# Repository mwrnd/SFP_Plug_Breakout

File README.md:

**Work-in-Progress** - [First Revision gerbers being tested](https://github.com/mwrnd/SFP_Plug_Breakout/releases/tag/v0.1-alpha).

# SFP_Plug_Breakout

Pluggable [SFP (SFF INF-8074i)](https://members.snia.org/document/dl/26184) and [SFP+ (SFF-8432)](https://members.snia.org/document/dl/25892) Module Breakout for developing SFP modules. PCB must be manufactured with a **1.0mm** thickness.

Similar Projects: [SFP-Breakout-Board](https://github.com/aewallin/SFP-Breakout-Board/tree/df46707f1ecbe9b7fed1791247dec31a45b60560), [SFP_BreakoutBoard](https://github.com/kingyoPiyo/SFP_BreakoutBoard), [SFP-Loopback-Board](https://github.com/aewallin/SFP-Loopback-Board), and [Sfp-breakout](https://osmocom.org/projects/misc-hardware/wiki/Sfp-breakout)(*osmocom.org*).

One trivial use is an [SFP Loopback](https://www.fs.com/products/109371.html):

## PCB Layout

Differential pair parameters were calculated based on a **board thickness of 1.0mm**.

## Schematic

The 0.1" Header is designed to accept jumpers for the **TX_FAULT**, **RX_LOS**, **TX_DISABLE**, and optionally **Rate-Select** signals.

**TX_FAULT**, **RX_LOS**, and **TX_DISABLE** jumpers need to be mounted for normal operation. These signals are pulled up to Vcc with 10k resistors but are Active-Low.

## Bill Of Materials

I have been testing with general purpose capacitors for the RX and TX DC-Blocking capacitors (C1, C2, C3, C4) but at <10Gbps bitrates. Capacitors will need to be sized smaller, 0402 or even 0201, and more effort would need to go into their selection for high bitrates. Look for [capacitors designed for high-frequency](https://www.digikey.ca/en/products/detail/passive-plus/0402BB104KW500/19186629).

| Designator(s)   | Part Number         | Quantity | Value   | Footprint                        | Availability                                                                                           |
| --------------- | ------------------- | -------- | ------- | -------------------------------- | ------------------------------------------------------------------------------------------------------ |
| C1, C2, C3, C4  | GRM1885C1H103JA01D  |        4 | 0.01uF  | Capacitor_SMD:C_0603_1608Metric  | [DigiKey](https://www.digikey.ca/en/products/detail/murata-electronics/GRM1885C1H103JA01D/4421555)     |
| R1, R2, R3      | RMCF0603ZT0R00      |        3 | 0-Ohm   | Resistor_SMD:R_0603_1608Metric   | [DigiKey](https://www.digikey.ca/en/products/detail/stackpole-electronics-inc/RMCF0603ZT0R00/1756908)  |
| R10, R11, R12   | RNCF0603DTE10K0     |        3 | 10k-Ohm | Resistor_SMD:R_0603_1608Metric   | [DigiKey](https://www.digikey.ca/en/products/detail/stackpole-electronics-inc/RNCF0603DTE10K0/1708145) |
| J6              | PH2-12-UA           |        1 | N/A     | Conn_02x06                       | [DigiKey](https://www.digikey.ca/en/products/detail/adam-tech/PH2-12-UA/9830397)                       |
| J2, J3, J4, J5  | CONUFL001-SMD-T     |        4 | N/A     | U.FL_w_Label:U.FL_Hirose_w_Label | [DigiKey](https://www.digikey.ca/en/products/detail/te-connectivity-linx/CONUFL001-SMD-T/7427732)      |
| None            | QPC02SXGN-RC        |        4 | N/A     | 1x2 0.1" Jumper                  | [DigiKey](https://www.digikey.ca/en/products/detail/sullins-connector-solutions/QPC02SXGN-RC/2618262)  |
| U.FL-to-U.FL    | 2015698-2           |        2 | N/A     | None - Optional Part for Testing | [DigiKey](https://www.digikey.ca/en/products/detail/te-connectivity-amp-connectors/2015698-2/1249186)  |

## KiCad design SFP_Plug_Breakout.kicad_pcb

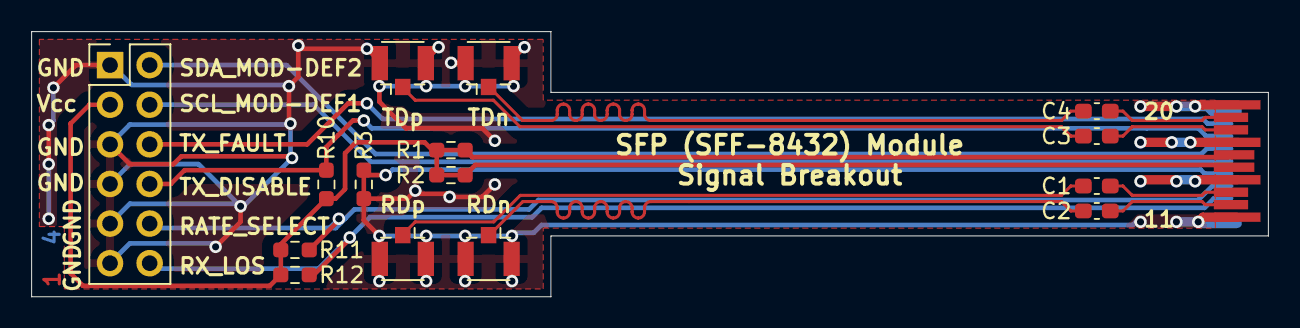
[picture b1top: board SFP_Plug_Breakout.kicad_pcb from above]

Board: 4 copper layers, 79.3 x 17.0 mm, 16 parts (0 on the bottom side), 17 nets.

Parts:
C1, C2, C3, C4: u01; C_0603_1608Metric_Pad1.08x0.95mm_HandSolder
J1: SFP+; SFP_Plug
J2: RDp; U.FL_Hirose_w_Label
J3: RDn; U.FL_Hirose_w_Label
J4: TDp; U.FL_Hirose_w_Label
J5: TDn; U.FL_Hirose_w_Label
J6: Conn_02x06_Odd_Even; PinHeader_2x06_P2.54mm_Vertical
R1, R2, R3: 0; R_0603_1608Metric_Pad0.98x0.95mm_HandSolder
R10, R11, R12: 10k; R_0603_1608Metric_Pad0.98x0.95mm_HandSolder

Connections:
/MOD-DEF0: J1.6 (MOD_ABS), R3.1
/R_N: C2.1, J1.12 (RD-)
/R_P: C1.1, J1.13 (RD+)
/T_N: C4.1, J1.19 (TD-)
/T_P: C3.1, J1.18 (TD+)
GND: J1.1 (VeeT), J1.10 (VeeR), J1.11 (VeeR), J1.14 (VeeR), J1.17 (VeeT), J1.20 (VeeT), J2.2 (Ext), J3.2 (Ext), J4.2 (Ext), J5.2 (Ext), J6.1, J6.5, J6.7, J6.9, J6.11, R3.2
RD_N: C2.2, J3.1 (In)
RD_P: C1.2, J2.1 (In)
RX_LOS: J1.8 (RX_LOS), J6.12, R12.2
Rate-Select: J1.7 (RS0), J6.10, R11.2
SCL_MOD-DEF1: J1.5 (SCL), J6.4
SDA_MOD-DEF2: J1.4 (SDA), J6.2
TD_N: C4.2, J5.1 (In)
TD_P: C3.2, J4.1 (In)
TX_DISABLE: J1.3 (TX_DISABLE), J6.8, R10.2
TX_FAULT: J1.2 (TX_FAULT), J6.6
VCC: J1.15 (VccR), J1.16 (VccT), J6.3, R1.1, R1.2, R2.1, R2.2, R10.1, R11.1, R12.1

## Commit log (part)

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2024-03-01 First Revision
2024-12-08 Added Bill of Materials
2026-03-13 Added Pictures
